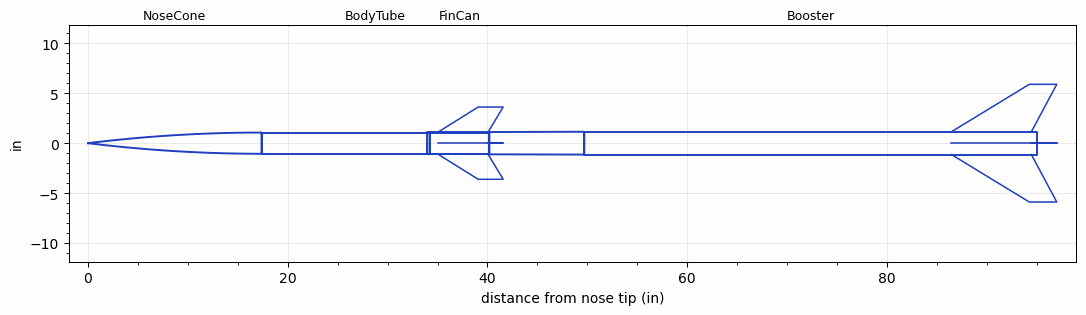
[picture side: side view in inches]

<RASAeroDocument>
 <FileVersion>2</FileVersion>
 <RocketDesign>
  <NoseCone>
   <Length>17.375</Length>
   <Diameter>2.125</Diameter>
   <Shape>Tangent Ogive</Shape>
   <Location>0</Location>
  </NoseCone>
  <BodyTube>
   <Length>22.818</Length>
   <Diameter>2.125</Diameter>
   <Location>17.375</Location>
  </BodyTube>
  <FinCan>
   <Length>6</Length>
   <Diameter>2.235</Diameter>
   <InsideDiameter>2.125</InsideDiameter>
   <Location>40.193</Location>
   <ShoulderLength>0.25</ShoulderLength>
   <Offset>-6</Offset>
   <Fin>
    <Count>4</Count>
    <Chord>5</Chord>
    <Span>2.5</Span>
    <SweepDistance>4</SweepDistance>
    <TipChord>2.5</TipChord>
    <Thickness>0.125</Thickness>
    <Location>5.125</Location>
    <AirfoilSection>Hexagonal</AirfoilSection>
    <FX1>2</FX1>
    <FX3>2</FX3>
   </Fin>
  </FinCan>
  <Booster>
   <Length>45.366</Length>
   <Diameter>2.285</Diameter>
   <InsideDiameter>2.235</InsideDiameter>
   <Location>40.193</Location>
   <ShoulderLength>9.5</ShoulderLength>
   <Fin>
    <Count>4</Count>
    <Chord>8</Chord>
    <Span>4.75</Span>
    <SweepDistance>7.794</SweepDistance>
    <TipChord>2.75</TipChord>
    <Thickness>0.18</Thickness>
    <Location>8.6</Location>
    <AirfoilSection>Hexagonal</AirfoilSection>
    <FX1>2</FX1>
    <FX3>2</FX3>
   </Fin>
  </Booster>
  <Surface>Rough Camouflage Paint</Surface>
  <ModifiedBarrowman>True</ModifiedBarrowman>
  <Turbulence>True</Turbulence>
  <UseBooster1>False</UseBooster1>
  <UseBooster2>False</UseBooster2>
 </RocketDesign>
 <LaunchSite>
  <Altitude>1344</Altitude>
  <Pressure>30.05</Pressure>
  <RodAngle>0</RodAngle>
  <RodLength>10</RodLength>
  <Temperature>63.76</Temperature>
  <WindSpeed>0</WindSpeed>
 </LaunchSite>
 <Recovery>
  <Altitude1>1000</Altitude1>
  <Altitude2>1000</Altitude2>
  <DeviceType1>None</DeviceType1>
  <DeviceType2>None</DeviceType2>
  <Event1>False</Event1>
  <Event2>False</Event2>
  <Size1>1</Size1>
  <Size2>1</Size2>
  <EventType1>None</EventType1>
  <EventType2>None</EventType2>
  <CD1>1.33</CD1>
  <CD2>1.33</CD2>
 </Recovery>
 <SimulationList>
  <Simulation>
   <SustainerEngine>K2144  (SRT)</SustainerEngine>
   <SustainerLaunchWt>5.67</SustainerLaunchWt>
   <SustainerNozzleDiameter>2.125</SustainerNozzleDiameter>
   <SustainerCG>29.69</SustainerCG>
   <SustainerIgnitionDelay>0.5</SustainerIgnitionDelay>
   <Booster1Engine>M3464LB  (Loki)</Booster1Engine>
   <Booster1LaunchWt>25.3</Booster1LaunchWt>
   <Booster1SeparationDelay>0</Booster1SeparationDelay>
   <Booster1IgnitionDelay>0</Booster1IgnitionDelay>
   <Booster1CG>68.41</Booster1CG>
   <Booster1NozzleDiameter>1.818</Booster1NozzleDiameter>
   <IncludeBooster1>True</IncludeBooster1>
   <Booster2Delay>0</Booster2Delay>
   <IncludeBooster2>False</IncludeBooster2>
   <TimetoApogee>41.81949</TimetoApogee>
   <MaxAltitude>46415.02</MaxAltitude>
   <MaxVelocity>4479.183</MaxVelocity>
  </Simulation>
 </SimulationList>
</RASAeroDocument>
